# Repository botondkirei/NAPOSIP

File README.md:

# NAPOSIP
[NAPOSIP Project Homepage](http://naposip.utcluj.ro "NAPOSIP's Homepage")

The intention of NAPOSIP Project is to create a fully synthesizable All-Digital Phase/Frequency Locked Loop (FS-ADPLL). 
Traditionally, ADPLLs are designed in a full custom IC design flow (including the digital components). Whenever the design 
is migrated to a new technology, almost every component has to be redesigned from scrach in the design kit (PDK) of the 
given technology. The scope of the project is to automate the design process of ADPLLs, an make use of place and route
method to obtain the layout of a PLL.

The common ADPLL topologies consists of several components, such as Voltage/Digitally Controlled Oscillators (V/DCO), 
high freqyuency presacller, programmable frequency dividers, FIR filters, Time-to-Digital Converters (TDC), etc.
Some components are better suited to be designed in a full custom IC design flow, others are better suited to be described 
in a HDL language, synthesized and autorouted by EDA tools.

This repostory hold the source code and related documentation of aformentioned components. As RTL descriptions are not suitable
for power, delay and area estimation it is encoureged to implement the components at gate level using stucutral descriptions. 
A gate level description is as close to a final netlist as possible and thus early power, delay and area assessment can be carried
out using Power and Area Aware Implementation Method, as developed in a related project [ELIB](https://github.com/botondkirei/ELib).

# Directory structure

For each key component in a PLL a "standalone" directory is reserved (with their own readme.md and contributing.md). 

## SLM - System Level Models

System level models of ADPLLs can be found in SLM directory. Usually this models are numerical models of PLLs, it is encoureged
to use Octave Gnu to describe de behavoir at system level. 

## DCO - Digitally controlled oscillator

## LPF - Lowpass Filter (loop filter)

## TDC - Time-to-Digital converter

## Misc - Miscellaneous

Other components: Frequency dividers, Flying Adder Synthesizer, etc.

# Project Related Publications

# Usefull Reference
https://ieeexplore.ieee.org/stamp/stamp.jsp?tp=&arnumber=6891375
https://ieeexplore.ieee.org/stamp/stamp.jsp?arnumber=8190103

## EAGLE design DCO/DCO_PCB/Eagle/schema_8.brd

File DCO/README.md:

# DCO - Digitally controlled oscillator

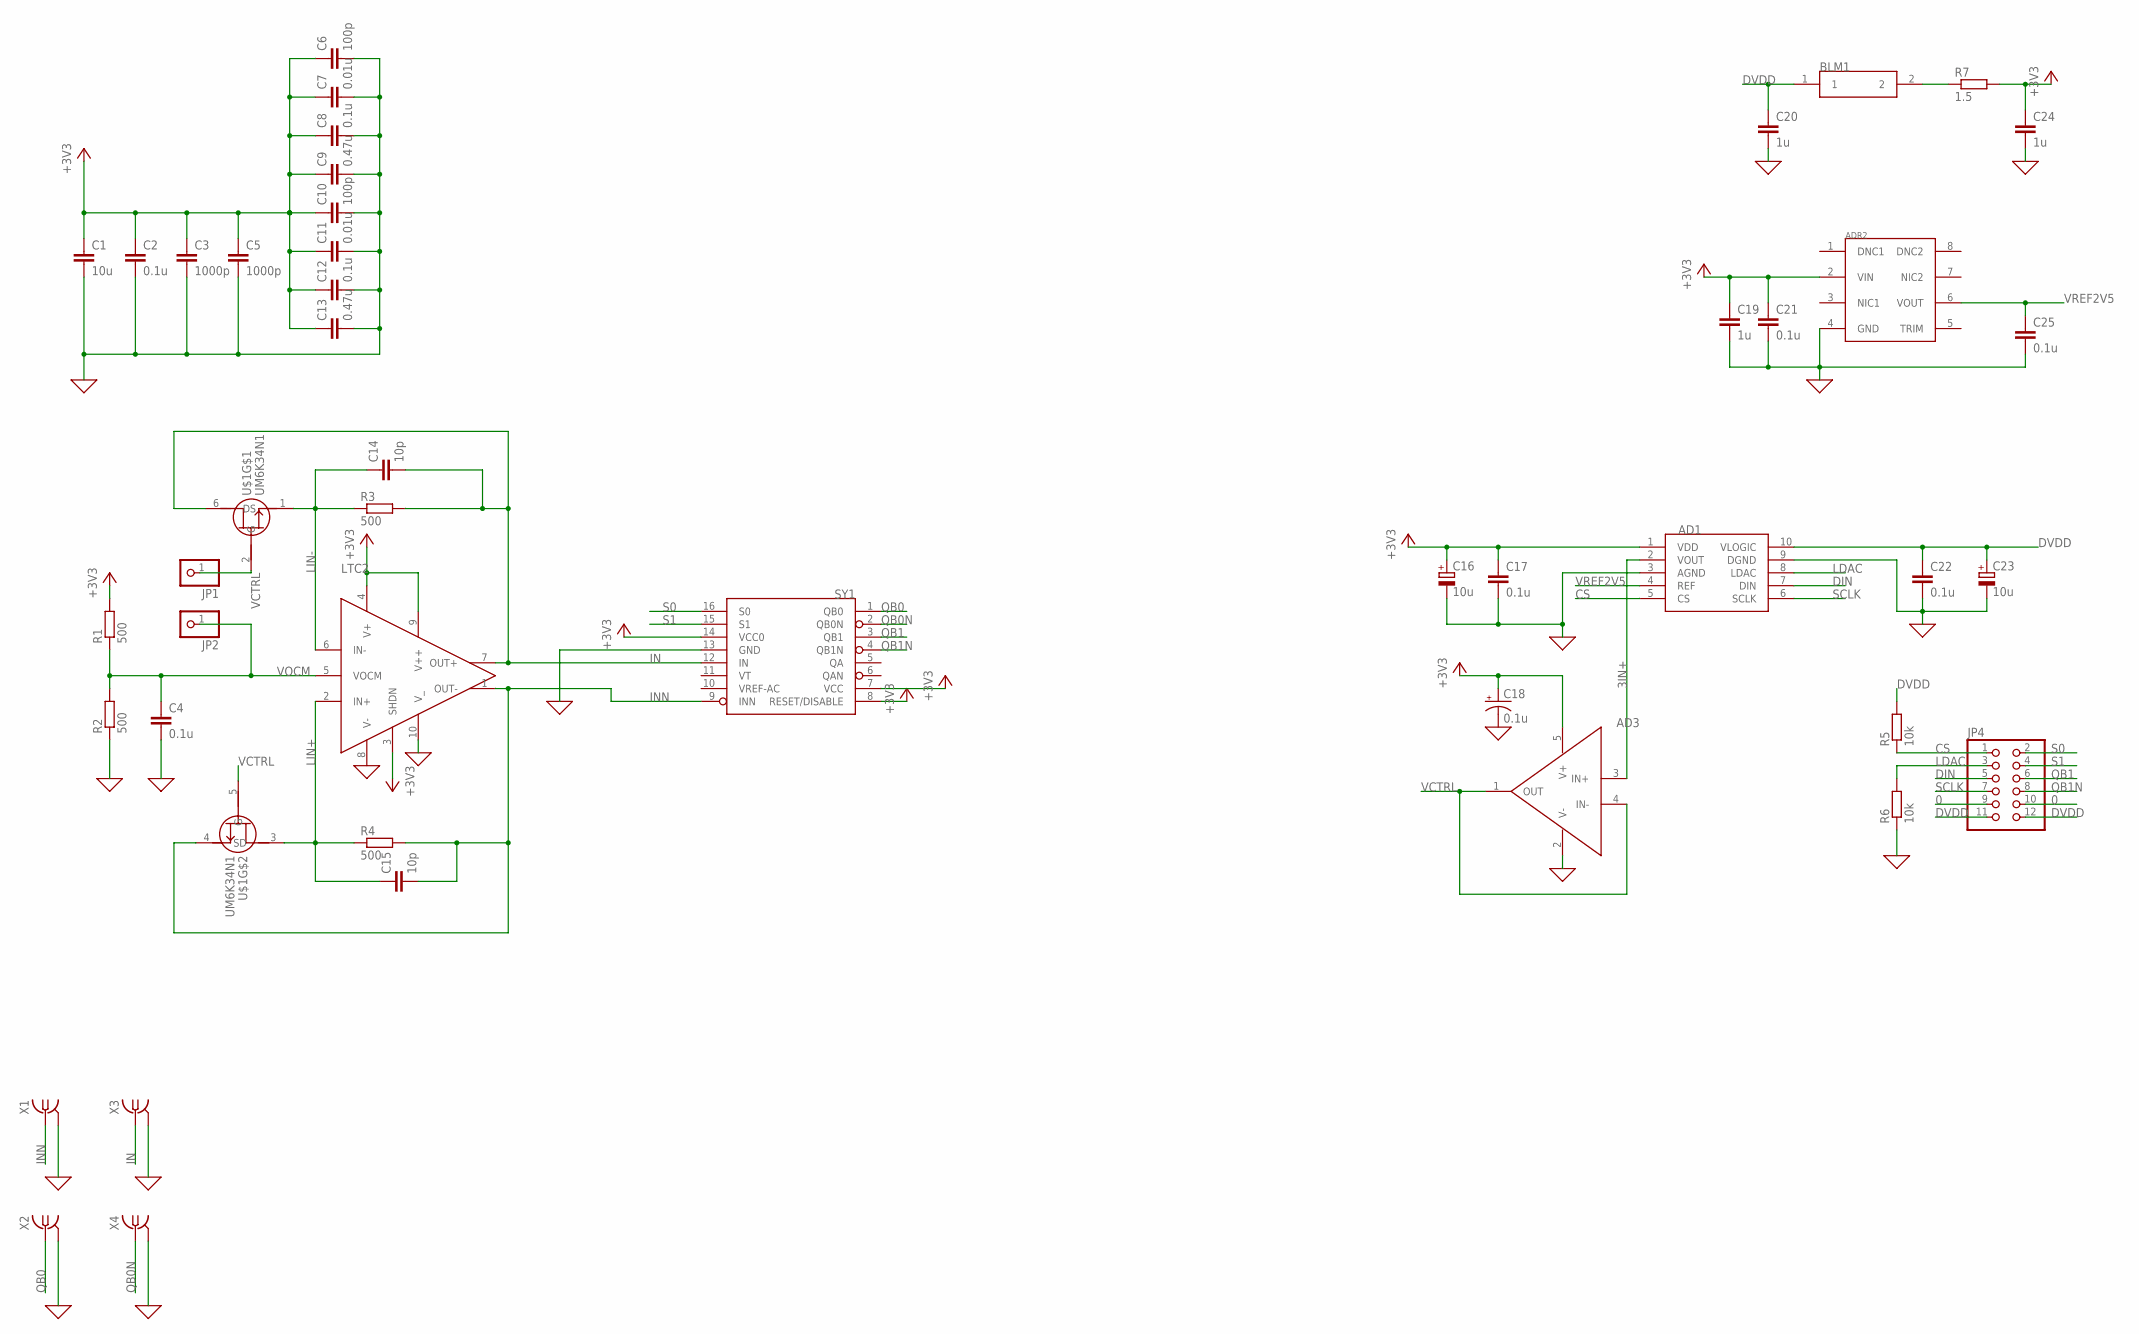
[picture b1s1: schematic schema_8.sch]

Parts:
AD1: 0; SOP50P490X110-10
AD3: 0; SOT95P280X145-5
ADR2: ADR441N; SOIC127P600X175-8
BLM1: 0; C1608
C1: 10u; C1210
C2, C4, C8, C12, C17, C21, C22, C25: 0.1u; C0603
C3, C5: 1000p; C1206
C6, C10: 100p; C0805
C7, C11: 0.01u; C1808
C9, C13: 0.47u; C1210
C14, C15: 10p; C0603
C16, C23: 10u; 153CLV-0405
C18: 0.1u; 153CLV-0405
C19, C20, C24: 1u; C0603
JP1, JP2: 0; 1X01
JP4: 0; 2X06/90
LTC2: 0; QFN50P350X250X80-10
R1, R2, R3, R4: 500; R0603
R5, R6: 10k; R0805
R7: 1.5; R0805
SY1: SY89873LN; QFN50P300X300X90-16
U$1: UM6K34N1; SOTFL65P210X100-6
X1, X2, X3, X4: SMA-142-0701-871/880; SMA-142-0701-871

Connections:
0: AD1.3 (AGND), AD1.9 (DGND), AD3.2 (V-), ADR2.4 (GND), C1.2, C2.2, C3.2, C4.2, C5.2, C6.2, C7.2, C8.2, C9.2, C10.2, C11.2, C12.2, C13.2, C16.-, C17.2, C18.-, C19.2, C20.2, C21.2, C22.2, C23.-, C24.2, C25.2, JP4.9, JP4.10, LTC2.8 (V-), LTC2.10 (V_), R2.1, R6.1, SY1.13 (GND), X1.2@1 (2), X1.2@2 (2), X1.2@3 (2), X1.2@4 (2), X2.2@1 (2), X2.2@2 (2), X2.2@3 (2), X2.2@4 (2), X3.2@1 (2), X3.2@2 (2), X3.2@3 (2), X3.2@4 (2), X4.2@1 (2), X4.2@2 (2), X4.2@3 (2), X4.2@4 (2)
3IN+: AD1.2 (VOUT), AD3.3 (IN+)
+3V3: AD1.1 (VDD), AD3.5 (V+), ADR2.2 (VIN), C1.1, C2.1, C3.1, C5.1, C6.1, C7.1, C8.1, C9.1, C10.1, C11.1, C12.1, C13.1, C16.+, C17.1, C18.+, C19.1, C21.1, C24.1, LTC2.3 (SHDN), LTC2.4 (V+), LTC2.9 (V++), R1.2, R7.2, SY1.7 (VCC), SY1.8 (RESET/DISABLE), SY1.14 (VCC0)
CS: AD1.5 (CS), JP4.1, R5.1
DIN: AD1.7 (DIN), JP4.5
DVDD: AD1.10 (VLOGIC), BLM1.1, C20.1, C22.1, C23.+, JP4.11, JP4.12, R5.2
IN: C14.2, LTC2.7 (OUT+), R3.2, SY1.12 (IN), U$1.6 (D), X3.1
INN: C15.2, LTC2.1 (OUT-), R4.2, SY1.9 (INN), U$1.4 (S), X1.1
LDAC: AD1.8 (LDAC), JP4.3, R6.2
LIN+: C15.1, LTC2.2 (IN+), R4.1, U$1.3 (D)
LIN-: C14.1, LTC2.6 (IN-), R3.1, U$1.1 (S)
unnamed: BLM1.2, R7.1
QB0: SY1.1 (QB0), X2.1
QB0N: SY1.2 (QB0N), X4.1
QB1: JP4.6, SY1.3 (QB1)
QB1N: JP4.8, SY1.4 (QB1N)
S0: JP4.2, SY1.16 (S0)
S1: JP4.4, SY1.15 (S1)
SCLK: AD1.6 (SCLK), JP4.7
VCTRL: AD3.1 (OUT), AD3.4 (IN-), JP1.1, U$1.2 (G), U$1.5 (G)
VOCM: C4.1, JP2.1, LTC2.5 (VOCM), R1.1, R2.2
VREF2V5: AD1.4 (REF), ADR2.6 (VOUT), C25.1

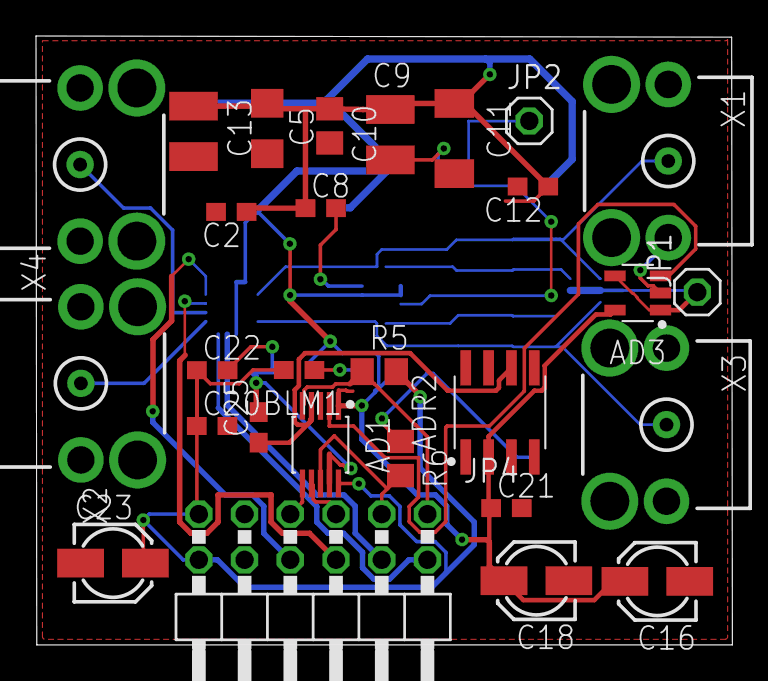
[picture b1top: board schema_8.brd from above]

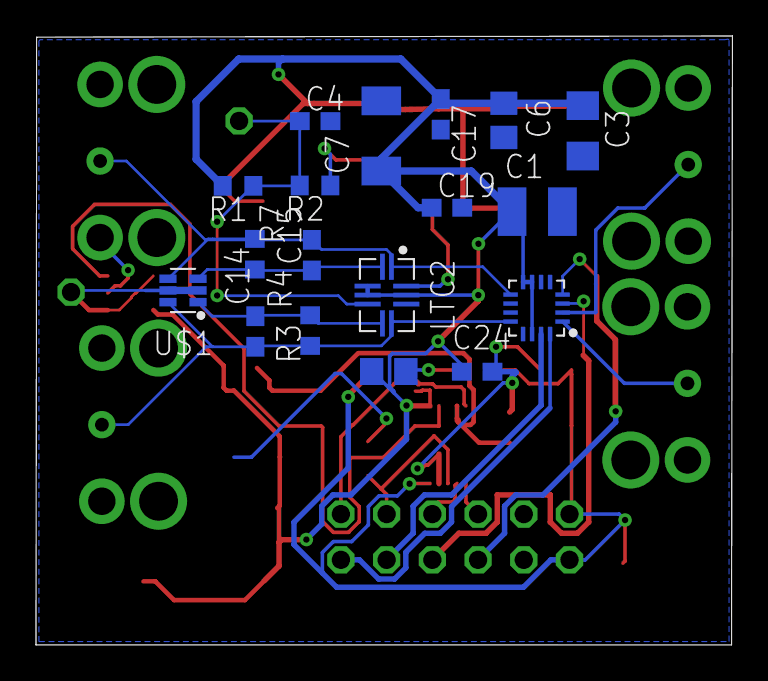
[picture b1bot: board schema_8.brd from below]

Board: 2 copper layers, 38.7 x 33.8 mm, 46 parts (18 on the bottom side), 22 nets.

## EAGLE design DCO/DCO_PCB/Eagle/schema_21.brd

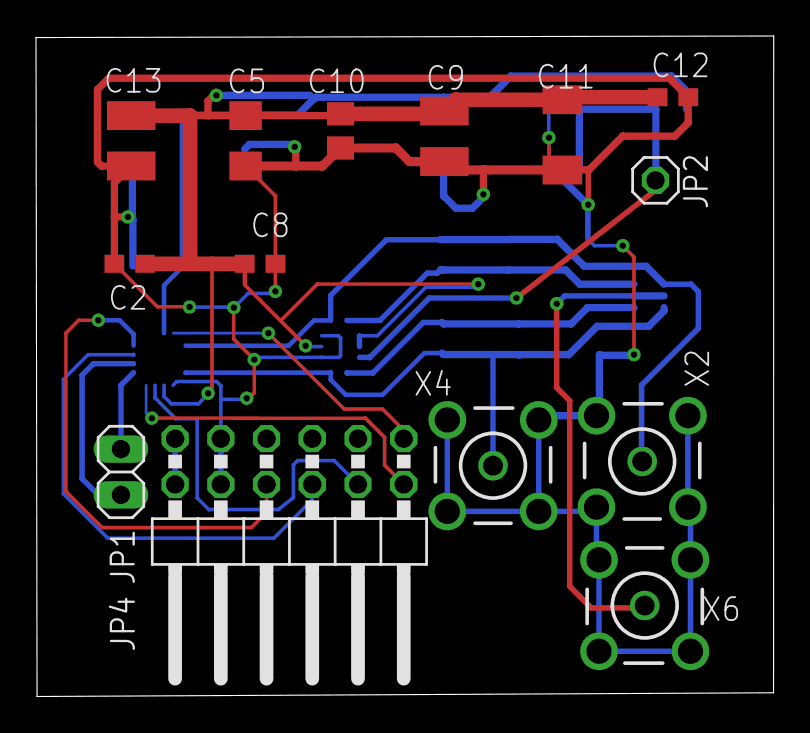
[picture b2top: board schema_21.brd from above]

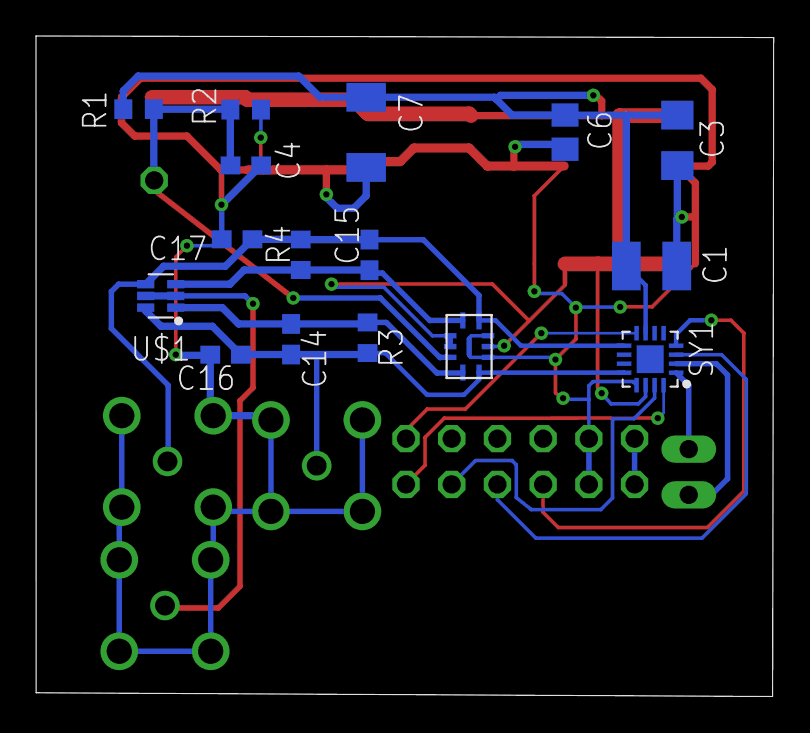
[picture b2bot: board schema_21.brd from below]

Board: 2 copper layers, 41.0 x 36.7 mm, 30 parts (16 on the bottom side), 16 nets.

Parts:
C1: 10u; C1210
C2, C4, C8, C12: 0.1u; C0603
C3, C5: 1000p; C1206
C6, C10: 100p; C0805
C7, C11: 0.01u; C1808
C9, C13: 0.47u; C1210
C14, C15, C16, C17: 10p; C0603
JP1: 1X02
JP2: 0; 1X01
JP4: 0; 2X06/90
LTC2: 0; LTC6409_1
R1, R2, R3, R4: 500; R0603
SY1: SY89873LN; QFN50P300X300X90-16
U$1: UM6K34N1; SOTFL65P210X100-6
X2, X4, X6: BU-SMB-V

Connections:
0: C1.2, C2.2, C3.2, C4.2, C5.2, C6.2, C7.2, C8.2, C9.2, C10.2, C11.2, C12.2, C13.2, C16.2, C17.2, JP4.9, JP4.10, LTC2.V-, LTC2.V--, LTC2.V---, R2.1, SY1.13, X2.2, X2.3, X2.4, X2.5, X4.2, X4.3, X4.4, X4.5, X6.2, X6.3, X6.4, X6.5
+3V3: C1.1, C2.1, C3.1, C5.1, C6.1, C7.1, C8.1, C9.1, C10.1, C11.1, C12.1, C13.1, LTC2.SHDN, LTC2.V+, LTC2.V++, R1.2, SY1.7, SY1.14
DVDD: JP4.11, JP4.12
IN: C14.2, C16.1, LTC2.OUT+, R3.2, SY1.12, U$1.6, X4.1
INN: C15.2, C17.1, LTC2.OUT-, R4.2, SY1.9, U$1.4, X2.1
LIN+: C15.1, LTC2.IN+, R4.1, U$1.3
LIN-: C14.1, LTC2.IN-, R3.1, U$1.1
QB0: JP1.1, SY1.1
QB0N: JP1.2, SY1.2
QB1: JP4.6, SY1.3
QB1N: JP4.8, SY1.4
RESET: JP4.1, SY1.8
S0: JP4.2, SY1.16
S1: JP4.4, SY1.15
VCTRL: U$1.2, U$1.5, X6.1
VOCM: C4.1, JP2.1, LTC2.VOCM, R1.1, R2.2

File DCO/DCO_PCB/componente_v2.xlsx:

ProTehno
Denumire componenta | Nr bucati | Package | Datasheet
AD5541A | 1 | MSOP10 | http://www.protehno.ro/ics/da-convertor/1843653/
AD8605 | 1 | 5SOT23 | http://www.protehno.ro/ics/amplifiers/operational/1838870/
LTC6409 | 1 | 10QFN | http://www.protehno.ro/ics/amplifiers/differential/2115799/
ADR441 | 1 | NSOIC-8 | http://www.protehno.ro/ics/voltage-references/1274158/
SY89873L | 1 | QFN-16 | http://www.protehno.ro/ics/clock/clock-generators---buffers/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
******************** | ****************** | ********** | *******************************************************************************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
Rezistori | Nr bucati | Valoare | Datasheet
 | 1 | 1.5 ohm | http://www.protehno.ro/resistors/fixed-resistors/chip-resist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
 | 4 | 500 ohm | 470ohm http://www.protehno.ro/resistors/fixed-resistors/chip-resist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
 |  |  | 510 ohm http://www.protehno.ro/resistors/fixed-resistors/chip-resist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
 | 2 | 10k | http://www.protehno.ro/resistors/fixed-resistors/chip-resist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
******************* | ******************** | ********** | *******************************************************************************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
Condensatoare | Nr bucati | Valoare | Datasheet
 | 2 | 10p | http://www.protehno.ro/capacitors/ceramic-multilayer/ceramic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
 | 2 | 100p | http://www.protehno.ro/oferte-speciale/capacitors/1828933p/
 | 2 | 0.01u =10n | http://www.protehno.ro/capacitors/ceramic-multilayer/ceramic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
 | 2 | 1000p | http://www.protehno.ro/capacitors/ceramic-multilayer/ceramic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
 | 8 | 0.1u=100n | http://www.protehno.ro/oferte-speciale/capacitors/432210p/
 | 2 | 0.47u | http://www.protehno.ro/capacitors/ceramic-multilayer/ceramic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
 | 3 | 1u | http://www.protehno.ro/capacitors/tantalum/tantalum--smd/1135061/
 | 1 | 10u | http://www.protehno.ro/capacitors/tantalum/tantalum--smd/113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
electrolitic | 1 | 0.1u=100n | http://www.protehno.ro/capacitors/aluminium-electrolytic/alu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
electrolitic | 2 | 10u | http://www.protehno.ro/capacitors/aluminium-electrolytic/alu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
Nr total condensatoare: | 25
******************* | ******************** | ********** | *******************************************************************************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
Alte componente:
Componenta | Denumire | Nr bucati | Datasheet
Tranzistor | 2N4416 | 2 | http://www.protehno.ro/transistors/jfet/1612627/
Ferita | BLM18EG221TN1D | 1 | http://www.protehno.ro/ferrites/ferrite-beads/1515717/
Conector SMA | SMA connector THT mounted | 4 | http://www.protehno.ro/connectors/rfcoaxial/rfcoax-connector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
Jumper |  | 2 | http://www.protehno.ro/connectors/accessories/jumpers-(busba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
Conector 1 & 2 |  | 1 | http://www.protehno.ro/connectors/pc-board/boardtoboard/1841229/
Total nr componente: | 47

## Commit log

2018-03-01 Add files via upload
    Componente considerate
2018-03-01 SI570 added to CVO list
2018-03-01 added Kicad project files
2018-03-19 as-a aduagta alimentarea in schema Signed-off-by: Botond Sandor Kirei <botond.kirei@bel.utcluj.ro>
2018-03-19 s-a adaugat gndd Signed-off-by: Botond Sandor Kirei <botond.kirei@bel.utcluj.ro>
2018-03-21 componente
    componente: Si550, Si571 si FMC
2018-03-26 added FIR directory
2018-03-28 added multiplication source files
2018-04-03 corectii
2018-04-03 file updates; added FAFS project files
2018-04-03 added source files
2018-04-10 LM339 si LT1011
    scheme LTSPICE
2018-04-19 Ring oscillator (that permits only an odd number of phases) was changed with an N phase clock generator (a clock signal is generated, then the signal is delayed)
2018-04-23 Modified FFA, to have 1 ns delay between cells and even number of phases
2018-05-07 ffa.xml
2018-05-07 dll.xml
2018-05-07 EFAFS.xml
2018-05-18 FAFS/EFAFS update
2018-05-18 added xilinx constraint to efafs
2018-05-18 added document to efafs/docs
2018-06-20 componente pentru placuta
2018-09-04 added files
2018-09-24 Create LICENSE
2018-09-24 Create CONTRIBUTING
2018-12-28 updates to dco schematic and octave scripts for modeling ADFLLs
2018-12-28 moved TDC models made in CPPSIM from ELIB repostory to NAPOSIP repostory
2019-01-17 Added ffa_rom.xml
2019-05-20 added README.md to TDC folder
2019-05-20 modifierd readme.md
2019-05-20 reorganized directory structure of NAPOSIP project
2019-05-24 copied source cod of TDC from PElib repostory to NAPOSIP repostory
2019-10-31 add multimodulus divider
